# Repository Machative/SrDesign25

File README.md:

EAGLE Project and Libraries for Senior Design '25

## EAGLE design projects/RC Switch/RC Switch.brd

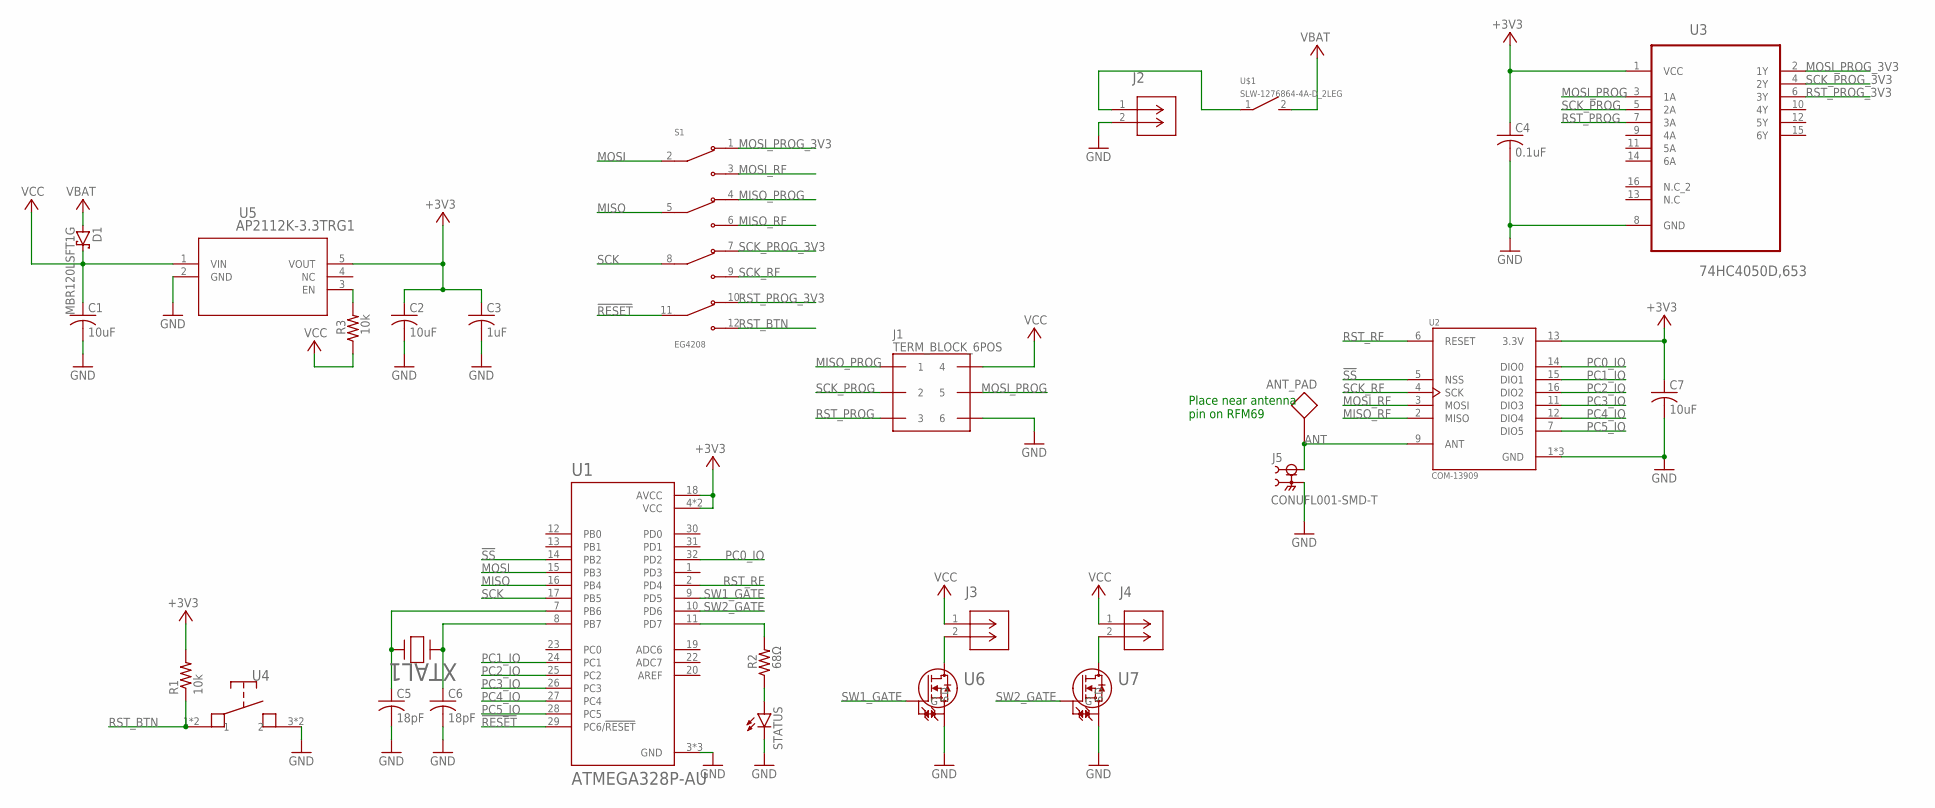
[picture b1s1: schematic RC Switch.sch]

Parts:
ANT_PAD: CIRCLE_PAD_40MIL
C1, C2, C7: 10uF; C1206
C3: 1uF; C1206
C4: 0.1uF; C1206
C5, C6: 18pF; C1206
D1: MBR120LSFT1G; DIOM3616X98N
J1: TERM_BLOCK_6POS
J2: S2B-PH-K-S(LF)(SN); CONN_S2B-PH-K-S_JST
J3, J4: 691137710002; CONN2_710002_WRE
J5: CONUFL001-SMD-T; LINX_CONUFL001-SMD-T
R1, R3: 10k; R1206
R2: 68Ω; R1206
S1: EG4208; SW_EG4208
STATUS: LEDCHIPLED_1206; CHIPLED_1206
U1: ATMEGA328P-AU; QFP80P900X900X120-32N
U2: COM-13909; MOD_COM-13909
U3: 74HC4050D,653; SOIC127P600X175-16N
U4: PTS526_SK15_SMTR2_LFS; SMT_FS
U5: AP2112K-3.3TRG1; SOT_RG1_DIO
U6, U7: DMN3023L-7; SOT-23_2P9X1P3_DIO
U$1: SLW-1276864-4A-D_2LEG
XTAL1: ABLS-8.000MHZ-B4-T; XTAL_ABLS2_ABR

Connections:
!RESET!: S1.11 (COM4), U1.29 (PC6/!RESET)
!SS!: U1.14 (PB2), U2.5 (NSS)
+3V3: C2.1, C3.1, C4.1, C7.1, R1.2, U1.4 (VCC), U1.6 (VCC), U1.18 (AVCC), U2.13 (3.3V), U3.1 (VCC), U5.5 (VOUT)
ANT: ANT_PAD.P$1, J5.1, U2.9 (ANT)
GND: C1.2, C2.2, C3.2, C4.2, C5.2, C6.2, C7.2, J1.6, J2.2, J5.2, J5.3 (2), STATUS.C, U1.3 (GND), U1.5 (GND), U1.21 (GND), U2.1 (GND), U2.8 (GND), U2.10 (GND), U3.8 (GND), U4.3 (2), U4.4 (2), U5.2 (GND), U6.2 (S), U7.2 (S)
MISO: S1.5 (COM2), U1.16 (PB4)
MISO_PROG: J1.1, S1.4 (NC2)
MISO_RF: S1.6 (NO2), U2.2 (MISO)
MOSI: S1.2 (COM1), U1.15 (PB3)
MOSI_PROG: J1.5, U3.3 (1A)
MOSI_PROG_3V3: S1.1 (NC1), U3.2 (1Y)
MOSI_RF: S1.3 (NO1), U2.3 (MOSI)
unnamed: J2.1, U$1.1
unnamed: C5.1, U1.7 (PB6), XTAL1.2
unnamed: C6.1, U1.8 (PB7), XTAL1.1
unnamed: R2.2, U1.11 (PD7)
unnamed: R2.1, STATUS.A
unnamed: J4.2, U7.3 (D)
unnamed: J3.2, U6.3 (D)
unnamed: R3.2, U5.3 (EN)
PC0_IO: U1.32 (PD2), U2.14 (DIO0)
PC1_IO: U1.24 (PC1), U2.15 (DIO1)
PC2_IO: U1.25 (PC2), U2.16 (DIO2)
PC3_IO: U1.26 (PC3), U2.11 (DIO3)
PC4_IO: U1.27 (PC4), U2.12 (DIO4)
PC5_IO: U1.28 (PC5), U2.7 (DIO5)
RST_BTN: R1.1, S1.12 (NO4), U4.1, U4.2 (1)
RST_PROG: J1.3, U3.7 (3A)
RST_PROG_3V3: S1.10 (NC4), U3.6 (3Y)
RST_RF: U1.2 (PD4), U2.6 (RESET)
SCK: S1.8 (COM3), U1.17 (PB5)
SCK_PROG: J1.2, U3.5 (2A)
SCK_PROG_3V3: S1.7 (NC3), U3.4 (2Y)
SCK_RF: S1.9 (NO3), U2.4 (SCK)
SW1_GATE: U1.9 (PD5), U6.1 (G)
SW2_GATE: U1.10 (PD6), U7.1 (G)
VBAT: D1.2 (A), U$1.2
VCC: C1.1, D1.1 (C), J1.4, J3.1, J4.1, R3.1, U5.1 (VIN)

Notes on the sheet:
Place near antenna pin on RFM69

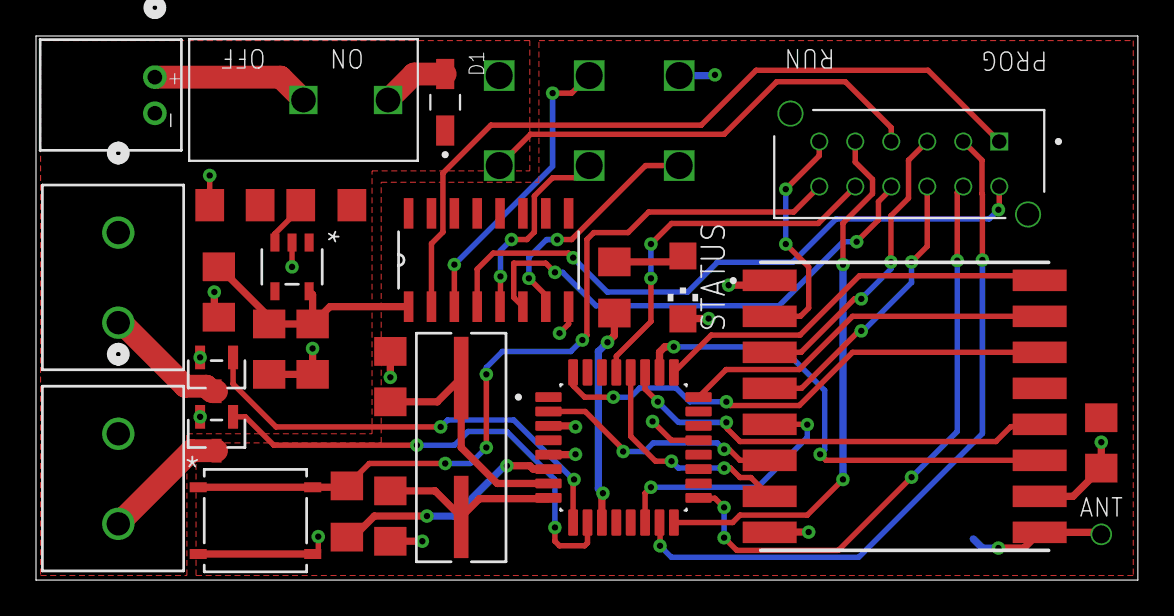
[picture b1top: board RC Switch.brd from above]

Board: 2 copper layers, 61.2 x 30.2 mm, 28 parts (1 on the bottom side), 38 nets.

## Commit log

2025-03-10 readme
2025-03-10 readme1
2025-03-10 Made some connections
2025-03-10 Sync to desktop
2025-03-11 More cleaning up, serial to ATMega pt 1
2025-03-11 stuff
2025-03-12 Back to ISP programming. Cleaned up BT module
2025-03-12 added gitignore
2025-03-12 Ignored more files
2025-03-12 Changes to BT connection
2025-03-12 Added DPDT and potentiometer
2025-03-14 Final touches
2025-03-14 removed reference schematics
2025-03-14 cleanup
2025-03-14 removed usb data line
2025-03-29 From PC
2025-03-29 Added ESP32 to PC version
2025-03-29 fixed library
2025-03-29 Incorporated ESP32

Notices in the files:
parts and their libraries:
COPYRIGHT: Copyright (C) 2024 Ultra Librarian. All rights reserved.
